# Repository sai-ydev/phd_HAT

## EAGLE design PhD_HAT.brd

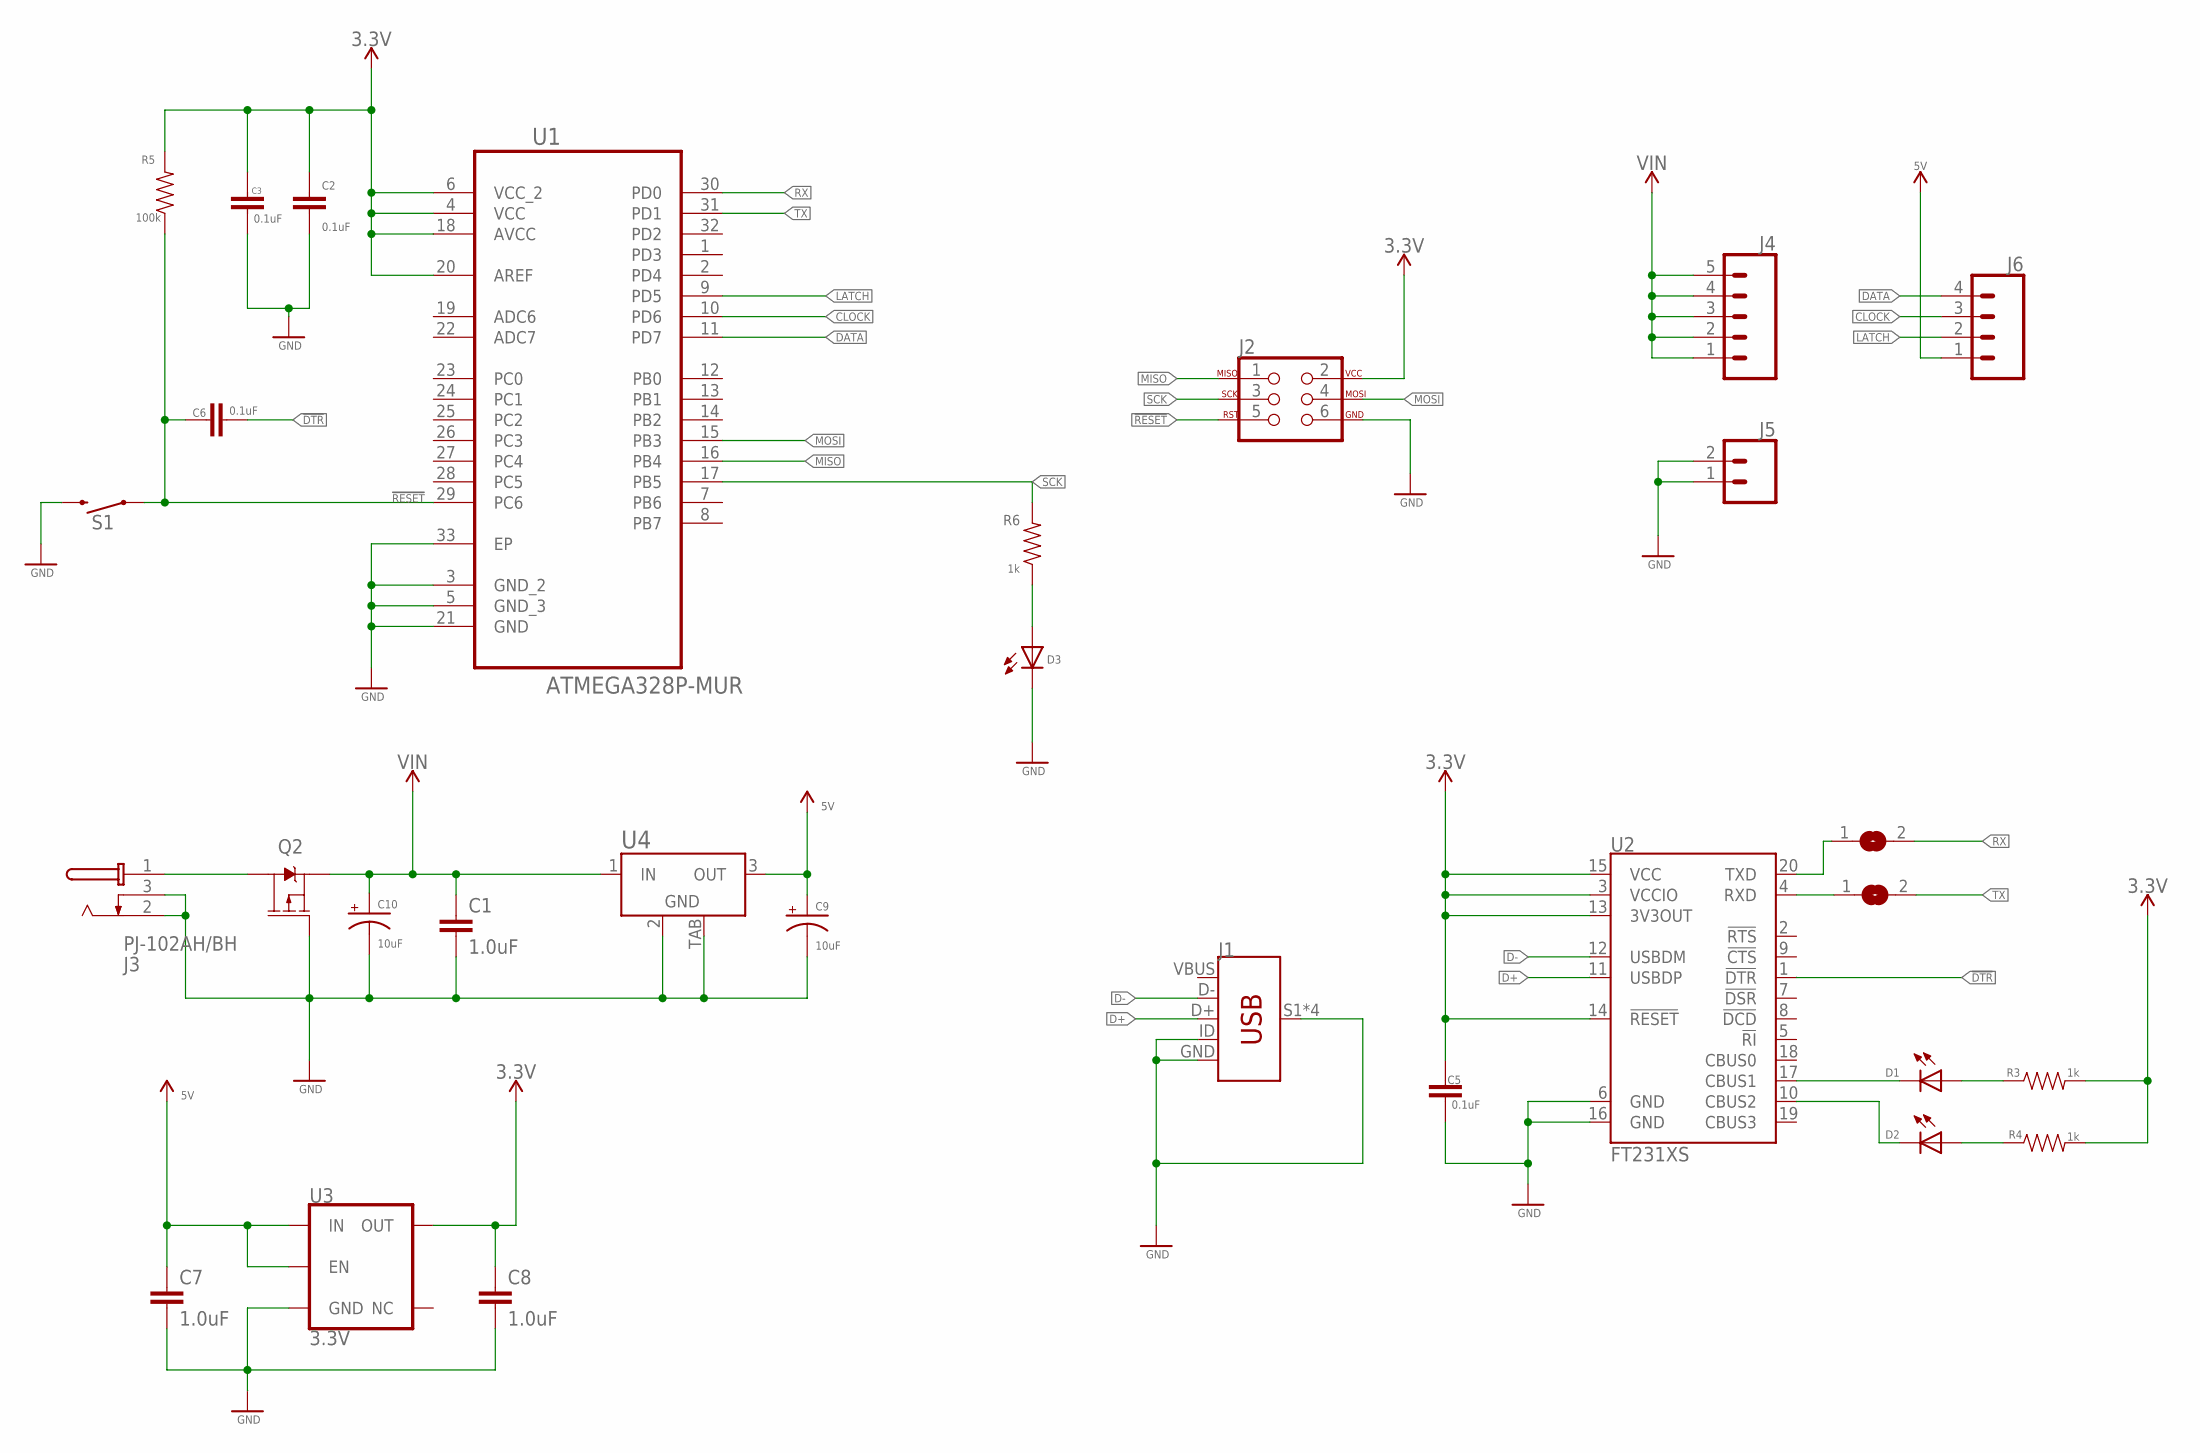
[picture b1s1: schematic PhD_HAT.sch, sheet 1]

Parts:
C1, C7, C8: 1.0uF; 0603
C2, C3, C5, C6: 0.1uF; 0603
C9, C10: 10uF; EIA3216
D1, D2, D3: LEDCHIP-LED0603; CHIP-LED0603
J1: USB_MINI-B_SMT; USB-MINIB
J2: AVR_SPI_PROG_3X2PTH; 2X3
J3: PJ-102AH/BH; PJ-102XH
J4: CONN_05SCREW; SCREWTERMINAL-3.5MM-5
J5: CONN_023.5MM; SCREWTERMINAL-3.5MM-2
J6: CONN_04SCREW; SCREWTERMINAL-3.5MM-4
Q2: 2.5A/30V/105mΩ; SOT23-3
R3, R4, R6: 1k; 0603
R5: 100k; 0603
S1: MOMENTARY-SWITCH-SPST-PTH-6.0MM; TACTILE_SWITCH_PTH_6.0MM
SJ1, SJ2: MICROBUILDER_SOLDERJUMPERREFLOW; MICROBUILDER_SOLDERJUMPER_REFLOW
U1: ATMEGA328P-MUR; QFN50P500X500X100-33N
U2: FT231XS; SSOP20_L
U3: 3.3V; SOT23-5
U4: MIC39100-5.0WS; SOT223

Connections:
3.3V: C2.1, C3.1, C5.1, C8.1, J2.2, R3.2, R4.2, R5.2, U1.4 (VCC), U1.6 (VCC_2), U1.18 (AVCC), U1.20 (AREF), U2.3 (VCCIO), U2.13 (3V3OUT), U2.14 (!RESET), U2.15 (VCC), U3.5 (OUT)
5V: C7.1, C9.+, J6.1, U3.1 (IN), U3.3 (EN), U4.3 (OUT)
!DTR: C6.2, U2.1 (!DTR)
!RESET: C6.1, J2.5, R5.1, S1.1, U1.29 (PC6)
CLOCK: J6.3, U1.10 (PD6)
D+: J1.D+, U2.11 (USBDP)
D-: J1.D-, U2.12 (USBDM)
DATA: J6.4, U1.11 (PD7)
GND: C1.2, C2.2, C3.2, C5.2, C7.2, C8.2, C9.-, C10.-, D3.C, J1.GND, J1.ID, J1.S1 (SHIELD), J1.S2 (SHIELD), J1.S3 (SHIELD), J1.S4 (SHIELD), J2.6, J3.2 (S), J3.3 (SS), J5.1, J5.2, Q2.1 (G), S1.3 (2), U1.3 (GND_2), U1.5 (GND_3), U1.21 (GND), U1.33 (EP), U2.6 (GND), U2.16 (GND), U3.2 (GND), U4.2 (GND), U4.TAB (GND); also elsewhere on the board
LATCH: J6.2, U1.9 (PD5)
MISO: J2.1, U1.16 (PB4)
MOSI: J2.4, U1.15 (PB3)
unnamed: D1.C, U2.17 (CBUS1)
unnamed: D2.C, U2.10 (CBUS2)
unnamed: D1.A, R3.1
unnamed: D2.A, R4.1
unnamed: D3.A, R6.1
unnamed: SJ1.1, U2.4 (RXD)
unnamed: SJ2.1, U2.20 (TXD)
unnamed: J3.1 (T), Q2.3 (D)
RX: SJ2.2, U1.30 (PD0); also elsewhere on the board
SCK: J2.3, R6.2, U1.17 (PB5)
TX: SJ1.2, U1.31 (PD1); also elsewhere on the board
VBUS: J1.VBUS
VIN: C1.1, C10.+, J4.1, J4.2, J4.3, J4.4, J4.5, Q2.2 (S), U4.1 (IN)

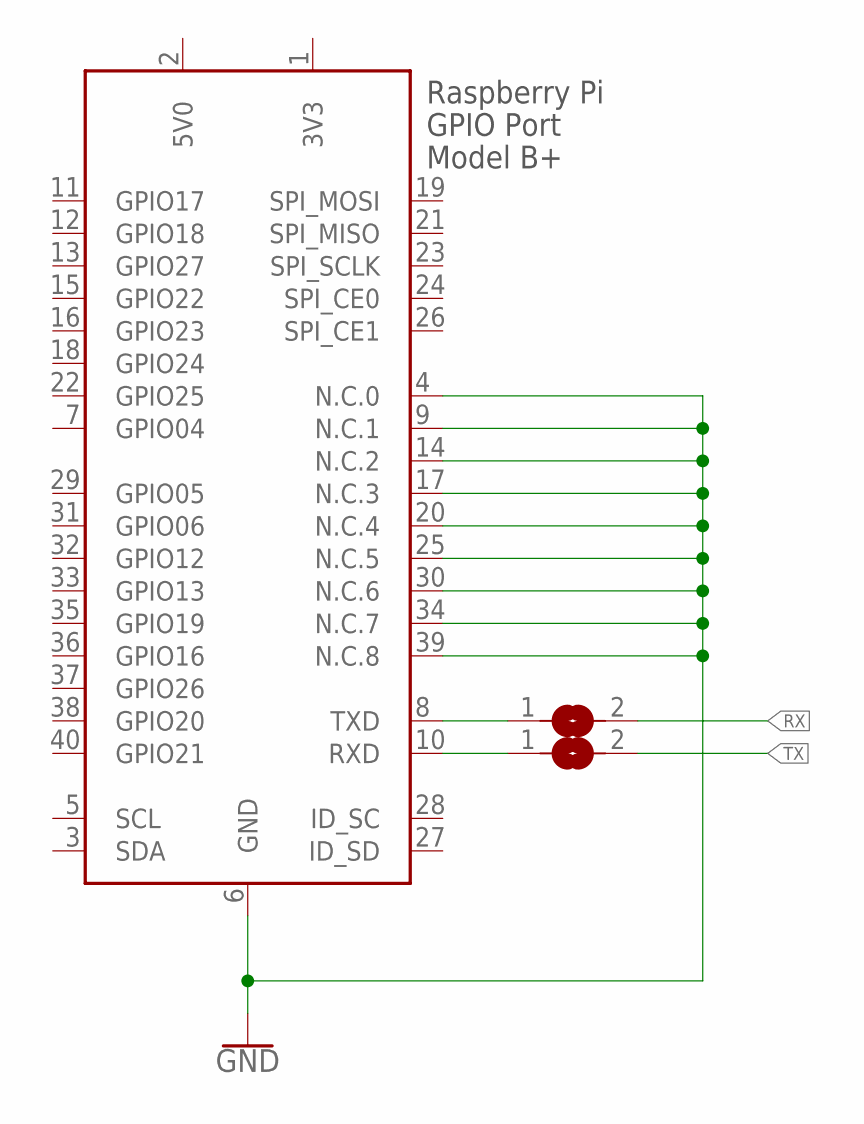
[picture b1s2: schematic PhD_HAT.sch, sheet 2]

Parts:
SJ3, SJ4: MICROBUILDER_SOLDERJUMPER; MICROBUILDER_SOLDERJUMPER_ARROW_NOPASTE
X1: RASPI_BOARD_B+_H; RASPI_BOARD_B+HAT

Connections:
3V3: X1.1 (3V3)
5V0: X1.2 (5V0)
GND: X1.4 (N.C.0), X1.6 (GND), X1.9 (N.C.1), X1.14 (N.C.2), X1.17 (N.C.3), X1.20 (N.C.4), X1.25 (N.C.5), X1.30 (N.C.6), X1.34 (N.C.7), X1.39 (N.C.8); also elsewhere on the board
unnamed: SJ3.1, X1.8 (TXD)
unnamed: SJ4.1, X1.10 (RXD)
RX: SJ3.2; also elsewhere on the board
TX: SJ4.2; also elsewhere on the board

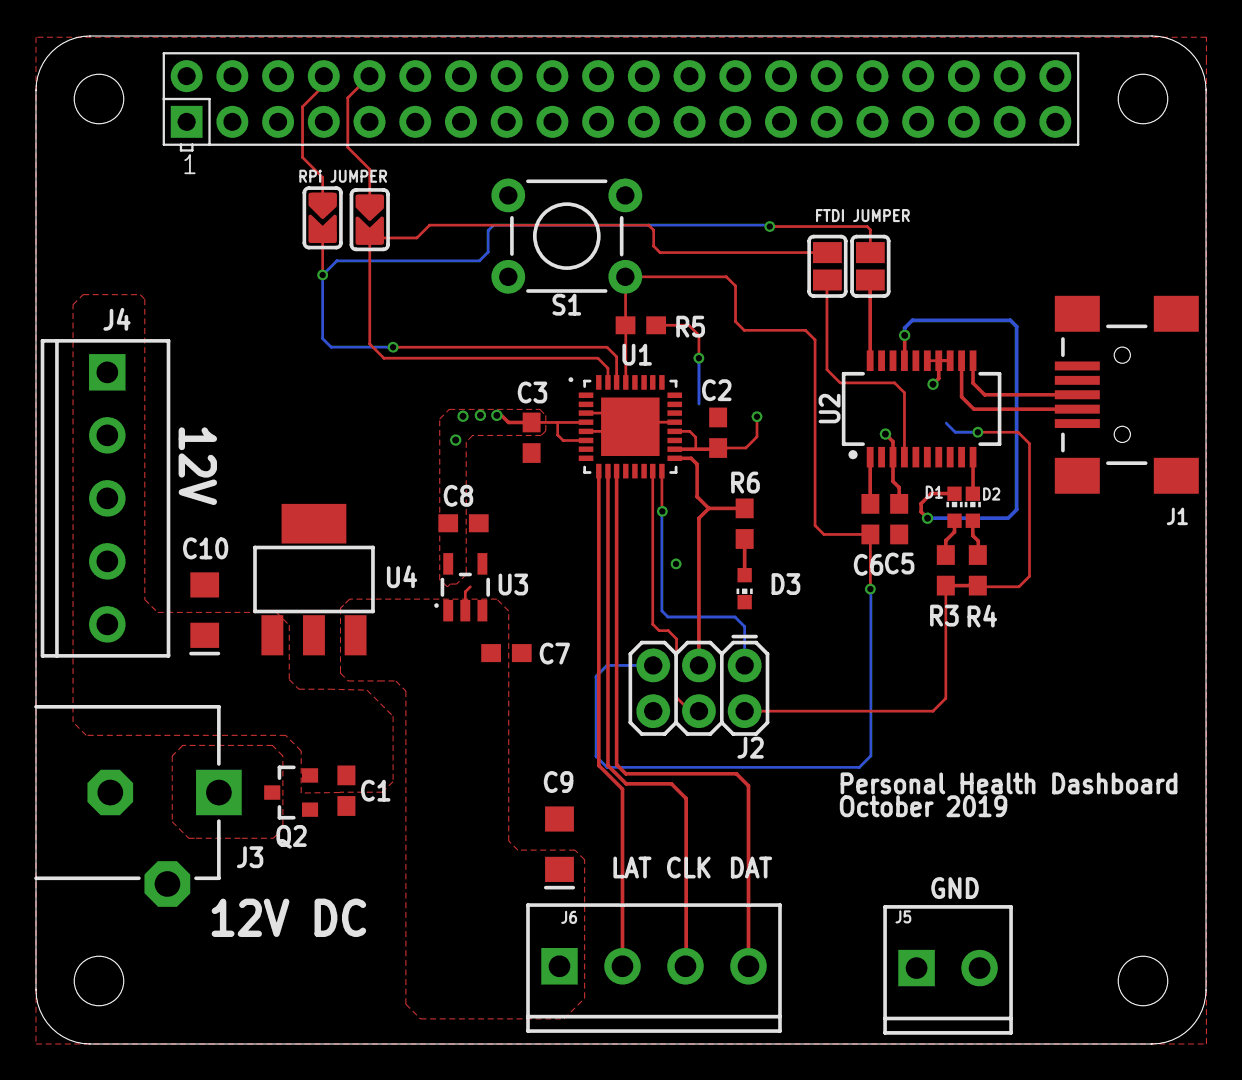
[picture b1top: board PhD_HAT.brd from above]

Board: 2 copper layers, 65.0 x 56.0 mm, 33 parts (0 on the bottom side), 26 nets.

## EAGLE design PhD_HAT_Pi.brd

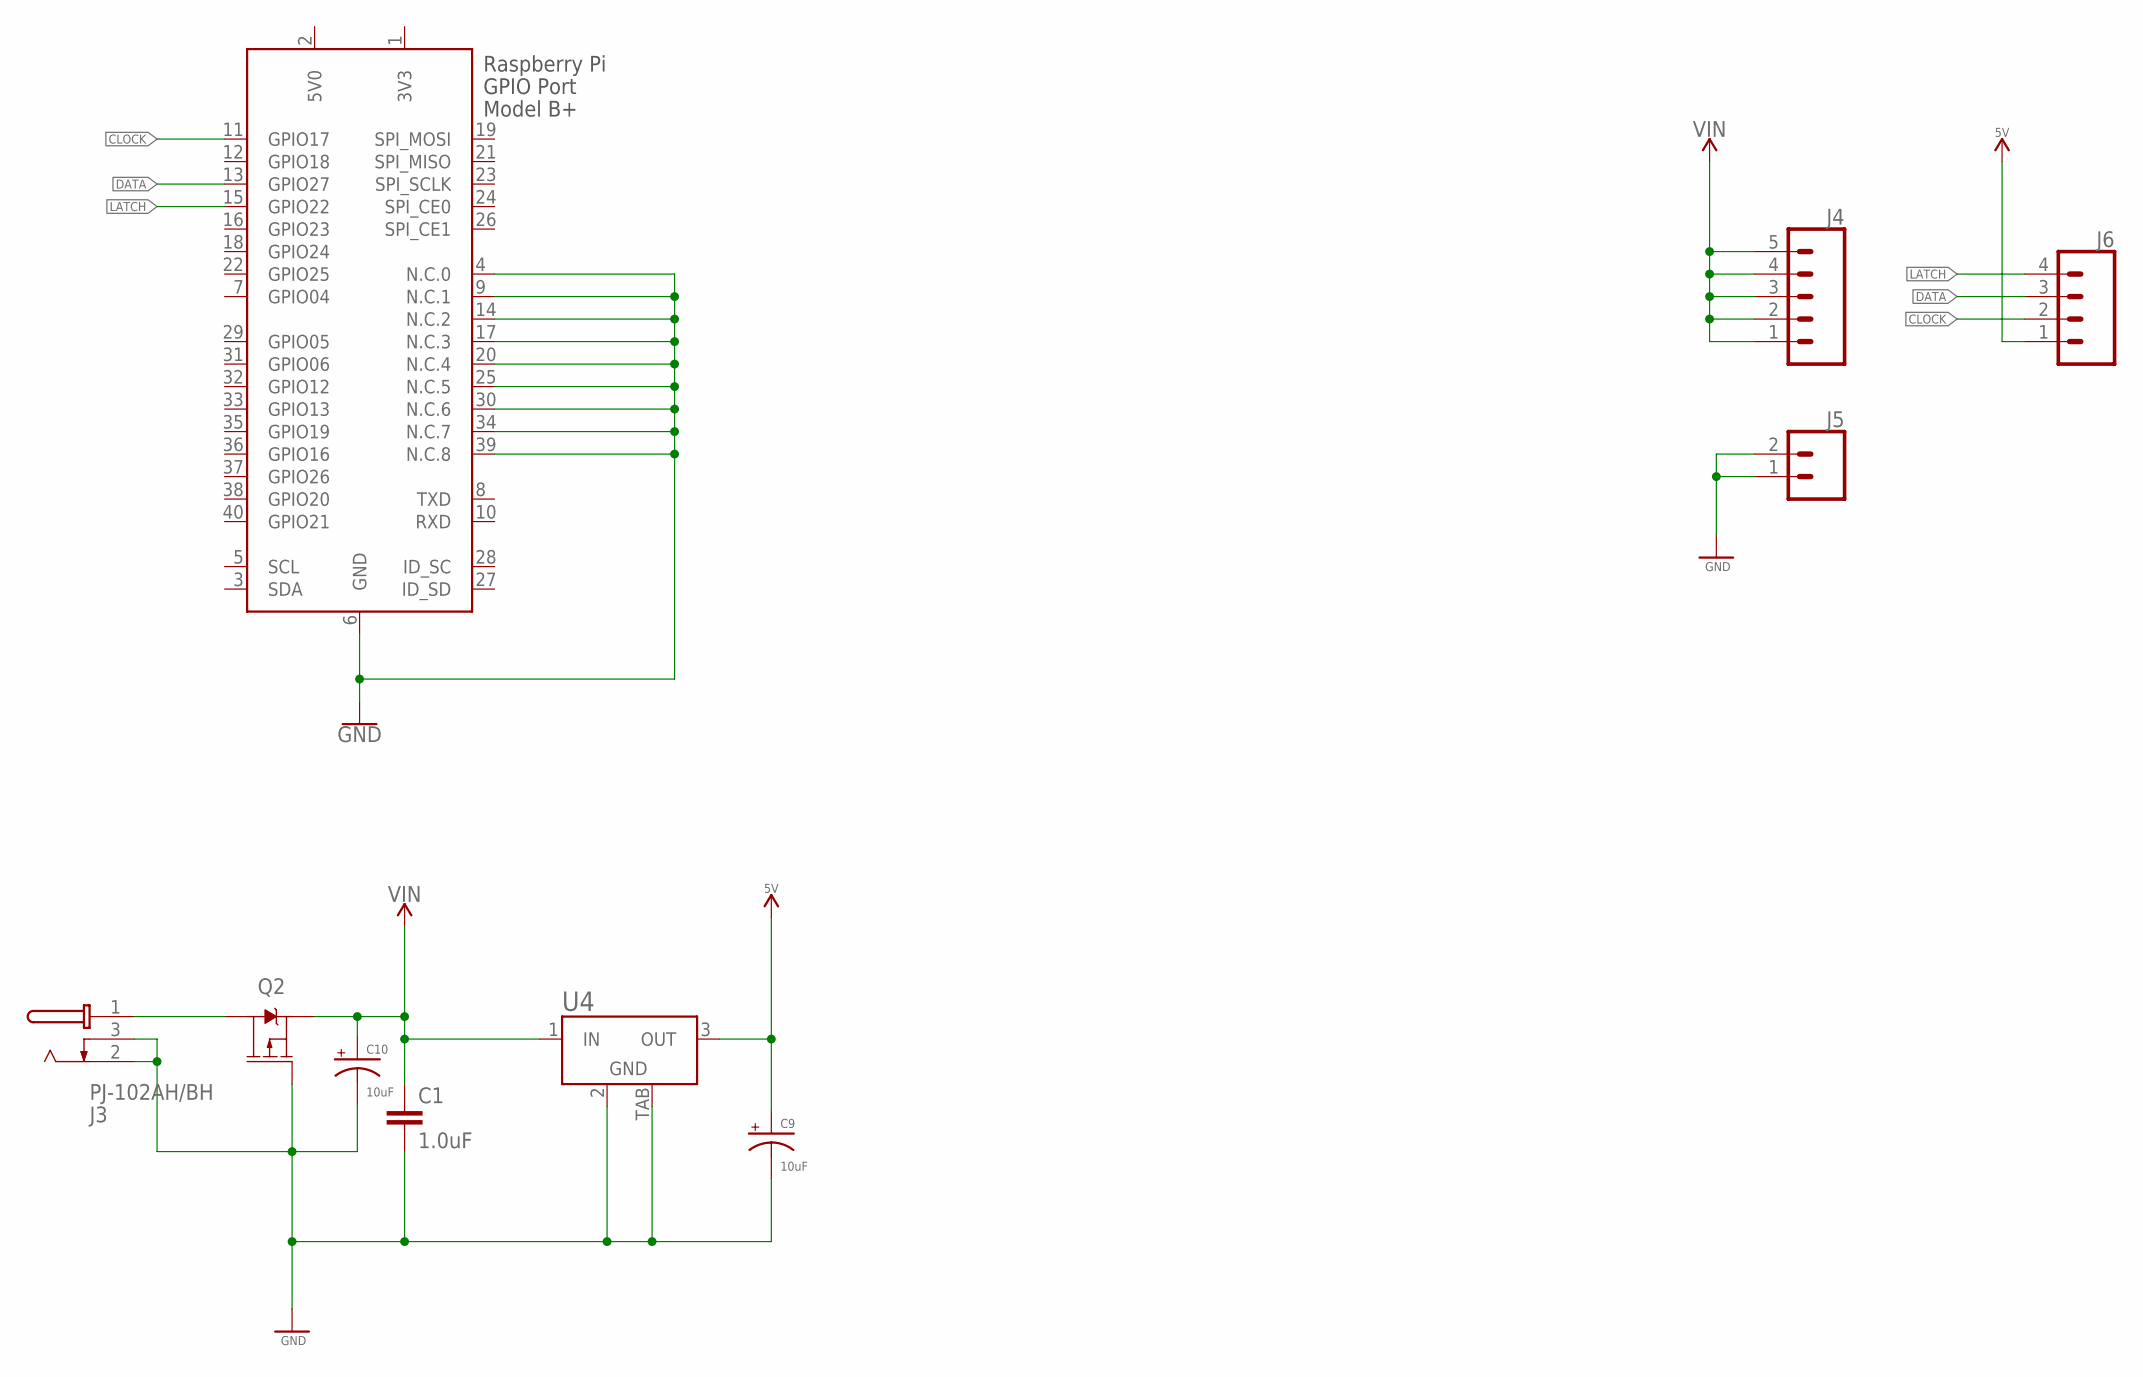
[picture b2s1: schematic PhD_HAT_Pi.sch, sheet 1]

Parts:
C1: 1.0uF; 0603
C9, C10: 10uF; EIA3216
J3: PJ-102AH/BH; PJ-102XH
J4: CONN_05SCREW; SCREWTERMINAL-3.5MM-5
J5: CONN_023.5MM; SCREWTERMINAL-3.5MM-2
J6: CONN_04SCREW; SCREWTERMINAL-3.5MM-4
Q2: 2.5A/30V/105mΩ; SOT23-3
U4: MIC39100-5.0WS; SOT223
X1: RASPI_BOARD_B+_H; RASPI_BOARD_B+HAT

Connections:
3V3: X1.1 (3V3)
5V: C9.+, J6.1, U4.3 (OUT)
5V0: X1.2 (5V0)
CLOCK: J6.2, X1.11 (GPIO17)
DATA: J6.3, X1.13 (GPIO27)
GND: C1.2, C9.-, C10.-, J3.2 (S), J3.3 (SS), J5.1, J5.2, Q2.1 (G), U4.2 (GND), U4.TAB (GND), X1.4 (N.C.0), X1.6 (GND), X1.9 (N.C.1), X1.14 (N.C.2), X1.17 (N.C.3), X1.20 (N.C.4), X1.25 (N.C.5), X1.30 (N.C.6), X1.34 (N.C.7), X1.39 (N.C.8)
LATCH: J6.4, X1.15 (GPIO22)
unnamed: J3.1 (T), Q2.3 (D)
VIN: C1.1, C10.+, J4.1, J4.2, J4.3, J4.4, J4.5, Q2.2 (S), U4.1 (IN)

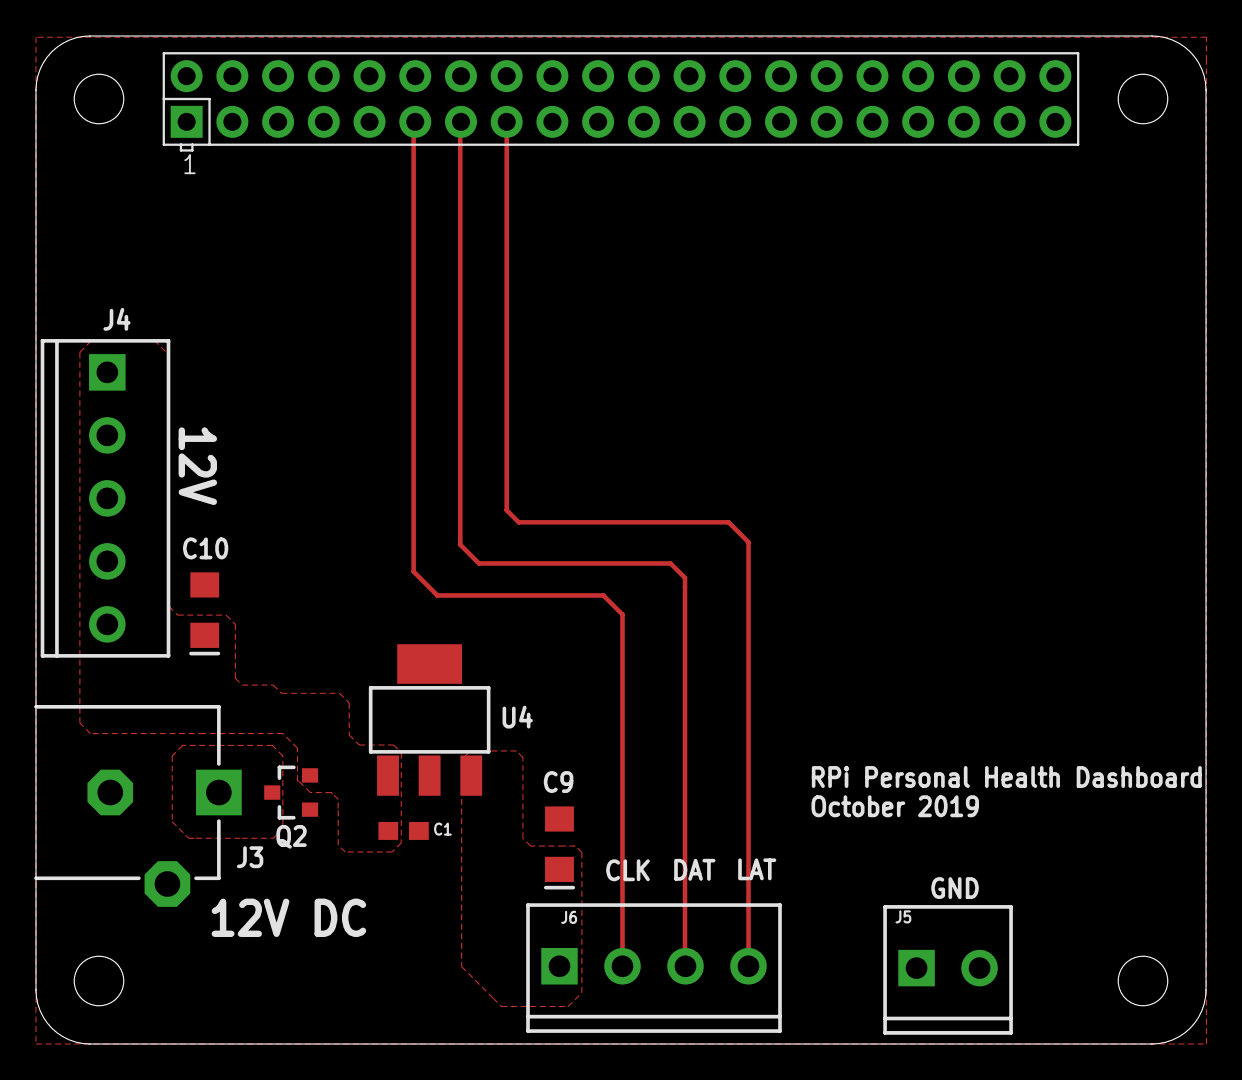
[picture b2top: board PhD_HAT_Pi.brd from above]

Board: 2 copper layers, 65.0 x 56.0 mm, 10 parts (0 on the bottom side), 7 nets.

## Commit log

2019-09-25 Check-in
2019-09-26 Checkin- version
2019-09-30 Check-in of design files
    A partial check-in to switch laptops
2019-09-30 check -in
2019-10-01 completed board file
2019-10-04 Checking in Raspberry Pi variant design
2019-10-11 Change of power flow sequence
    The max input voltage for the 3.3V regulator is 6V. The design was originally designed to receive 12V. This smoked the regulator. Changed the design to receive input from a 5V regulator.

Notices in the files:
parts and their libraries:
SparkFun-Capacitors: Licensing: Creative Commons ShareAlike 4.0 International - https://creativecommons.org/licenses/by-sa/4.0
con-cuistack: Copyright (C) 2008, Bob Starr
